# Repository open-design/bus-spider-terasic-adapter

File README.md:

UEXT adapter board for Terasic FPGA development boards with 40-pin expansion headers.

## Schematic

## BOM

| name | designation | designator | quantity | supply | datasheets |
| ---  | ---         | ---        | ---      | ---    | ---        |
| CONNFLY BH-10 | Conn_02x05_Odd_Even | J5,J2,J3,J4 | 4 |  [electronshik.ru](https://www.electronshik.ru/item/CONNFLY/BH-10)<br /> | [pdf](https://static.chipdip.ru/lib/463/DOC002463525.pdf) |
| CONNFLY BH-40 | Conn_02x20_Odd_Even | J1 | 1 |  [electronshik.ru](https://www.electronshik.ru/item/CONNFLY/BH-40)<br /> | [pdf](https://static.chipdip.ru/lib/463/DOC002463525.pdf) |
| Noname LED 1206 | LED | D1 | 1 |  [chipster.ru](https://chipster.ru/catalog/components/optic/leds/smd-led/3029.html)<br /> | no pdf |
| ONS MC14066BDR2G | 4066 | U2 | 1 |  [electronshik.ru](https://www.electronshik.ru/item/ONS/MC14066BDR2G)<br /> [digikey.com](https://www.digikey.com/products/en?keywords=MC14066BDR2G)<br /> [mouser.com](https://mouser.com/Search/Refine.aspx?Keyword=MC14066BDR2G)<br /> [farnell.com](https://uk.farnell.com/search?st=MC14066BDR2G)<br /> | [pdf](https://www.onsemi.com/pub/Collateral/MC14066B-D.PDF) |
| TI TPS79333-EP | TPS79333-EP | U1 | 1 |  [electronshik.ru](https://www.electronshik.ru/item/TI/TPS79333DBVR)<br /> [digikey.com](https://www.digikey.com/products/en?keywords=TPS79333DBVR)<br /> [mouser.com](https://mouser.com/Search/Refine.aspx?Keyword=TPS79333DBVR)<br /> [farnell.com](https://uk.farnell.com/search?st=TPS79333DBVR)<br /> | [pdf](http://www.ti.com/lit/ds/symlink/tps793.pdf) |
| YAGEO CC1206KKX7R8BB106 | 10uF | C3 | 1 |  [electronshik.ru](https://www.electronshik.ru/item/YAG/CC1206KKX7R8BB106)<br /> [digikey.com](https://www.digikey.com/products/en?keywords=CC1206KKX7R8BB106)<br /> [mouser.com](https://mouser.com/Search/Refine.aspx?Keyword=CC1206KKX7R8BB106)<br /> [farnell.com](https://uk.farnell.com/search?st=CC1206KKX7R8BB106)<br /> | [pdf](http://www.yageo.com/exep/pages/download/literatures/ProductSelectionGuide_2018_Final.pdf#page=112) |
| YAGEO CC1206KRX7R9BB103 | 10nF | C2 | 1 |  [electronshik.ru](https://www.electronshik.ru/item/YAG/CC1206KRX7R9BB103)<br /> [digikey.com](https://www.digikey.com/products/en?keywords=CC1206KRX7R9BB103)<br /> [mouser.com](https://mouser.com/Search/Refine.aspx?Keyword=CC1206KRX7R9BB103)<br /> [farnell.com](https://uk.farnell.com/search?st=CC1206KRX7R9BB103)<br /> | [pdf](http://www.yageo.com/exep/pages/download/literatures/ProductSelectionGuide_2018_Final.pdf#page=112) |
| YAGEO CC1206KRX7R9BB104 | 0.1uF | C1,C4 | 2 |  [electronshik.ru](https://www.electronshik.ru/item/YAG/CC1206KRX7R9BB104)<br /> [digikey.com](https://www.digikey.com/products/en?keywords=CC1206KRX7R9BB104)<br /> [mouser.com](https://mouser.com/Search/Refine.aspx?Keyword=CC1206KRX7R9BB104)<br /> [farnell.com](https://uk.farnell.com/search?st=CC1206KRX7R9BB104)<br /> | [pdf](http://www.yageo.com/exep/pages/download/literatures/ProductSelectionGuide_2018_Final.pdf#page=112) |
| YAGEO RC1206FR-0710KL | 10K | R3,R4 | 2 |  [electronshik.ru](https://www.electronshik.ru/item/YAG/RC1206FR-0710KL)<br /> [digikey.com](https://www.digikey.com/products/en?keywords=RC1206FR-0710KL)<br /> [mouser.com](https://mouser.com/Search/Refine.aspx?Keyword=RC1206FR-0710KL)<br /> [farnell.com](https://uk.farnell.com/search?st=RC1206FR-0710KL)<br /> | [pdf](http://www.yageo.com/exep/pages/download/literatures/ProductSelectionGuide_2018_Final.pdf#page=8) |
| YAGEO RC1206FR-071K1L | 1.1K | R2 | 1 |  [electronshik.ru](https://www.electronshik.ru/item/YAG/RC1206FR-071K1L)<br /> [digikey.com](https://www.digikey.com/products/en?keywords=RC1206FR-071K1L)<br /> [mouser.com](https://mouser.com/Search/Refine.aspx?Keyword=RC1206FR-071K1L)<br /> [farnell.com](https://uk.farnell.com/search?st=RC1206FR-071K1L)<br /> | [pdf](http://www.yageo.com/exep/pages/download/literatures/ProductSelectionGuide_2018_Final.pdf#page=8) |
| YAGEO RC1206FR-074K7L | 4.7K | R1 | 1 |  [electronshik.ru](https://www.electronshik.ru/item/YAG/RC1206FR-074K7L)<br /> [digikey.com](https://www.digikey.com/products/en?keywords=RC1206FR-074K7L)<br /> [mouser.com](https://mouser.com/Search/Refine.aspx?Keyword=RC1206FR-074K7L)<br /> [farnell.com](https://uk.farnell.com/search?st=RC1206FR-074K7L)<br /> | [pdf](http://www.yageo.com/exep/pages/download/literatures/ProductSelectionGuide_2018_Final.pdf#page=8) |

## Links

* [InnovateFPGA 2018 | EM099 | Bus Spider](http://www.innovatefpga.com/cgi-bin/innovate/teams2018.pl?Id=EM099)
* [Bus Spider: flexible open source hacker multi-tool](https://github.com/miet-riscv-workgroup/de10-nano-bus-spider)
* [Olimex UEXT board to board connector](https://www.olimex.com/Products/Modules/UEXT/)
* [Dangerous Prototypes: Bus Pirate v3.6](http://dangerousprototypes.com/docs/Bus_Pirate_v3.6)

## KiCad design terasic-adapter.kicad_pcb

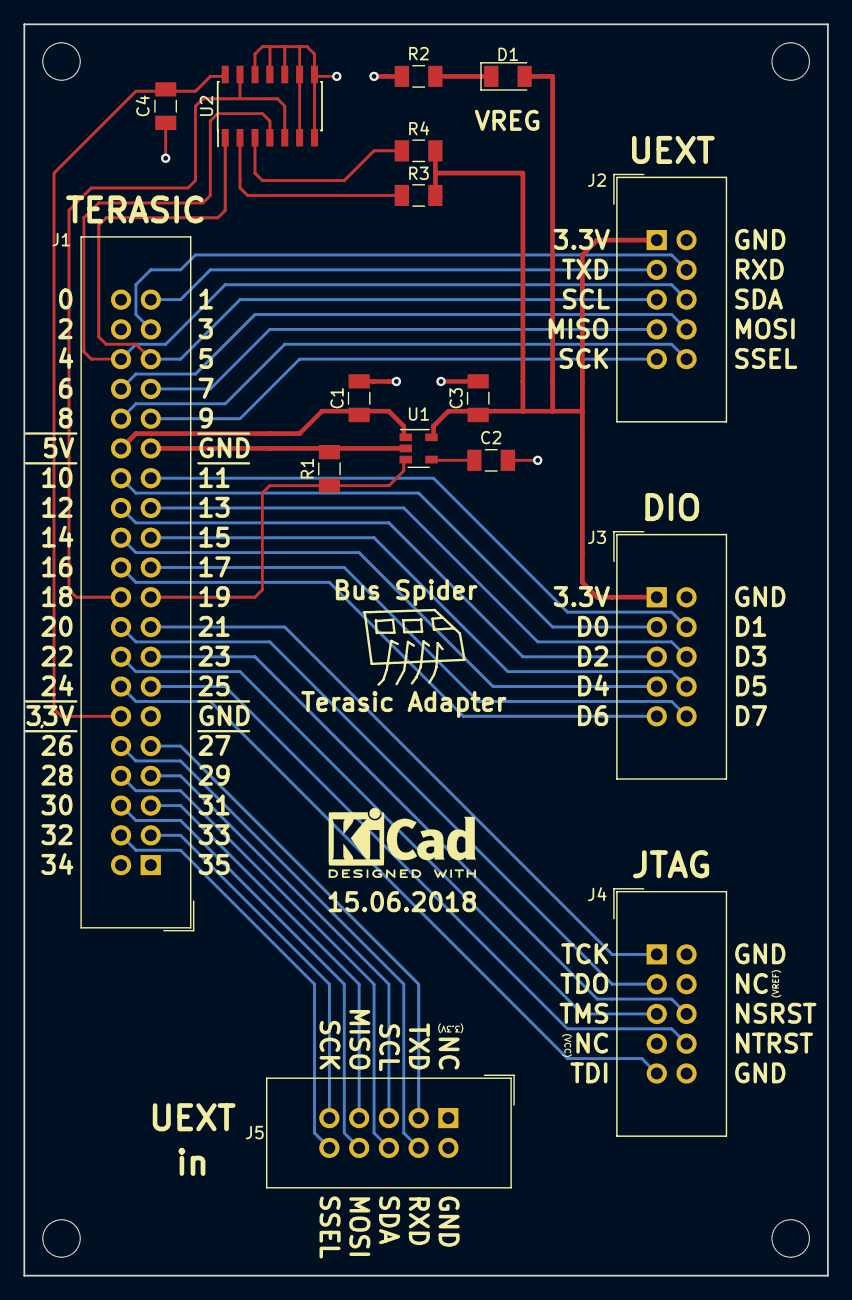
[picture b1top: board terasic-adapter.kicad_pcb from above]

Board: 2 copper layers, 68.6 x 106.8 mm, 20 parts (0 on the bottom side), 40 nets.

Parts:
C1, C4: 0.1uF; C_1206_3216Metric
C2: 10nF; C_1206_3216Metric
C3: 10uF; C_1206_3216Metric
D1: LED; LED_1206_3216Metric
J1: Conn_02x20_Odd_Even; IDC-Header_2x20_P2.54mm_Vertical
J2, J3, J4, J5: Conn_02x05_Odd_Even; IDC-Header_2x05_P2.54mm_Vertical
MK1, MK2, MK3, MK4: Mounting_Hole; MountingHole_3.2mm_M3
R1: 4.7K; R_1206_3216Metric
R2: 1.1K; R_1206_3216Metric
R3, R4: 10K; R_1206_3216Metric
U1: TPS79333-EP; SOT-23-5
U2: 4066; SOIC-14_3.9x8.7mm_P1.27mm

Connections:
+3V3: C4.2, J1.12, U2.14
+5V: C1.1, J1.30, U1.1
/GPIO1: J1.39, J2.3
/GPIO3: J1.37, J2.4
/GPIO4: J1.36, J2.6, U2.4
/GPIO5: J1.35, J2.5, U2.1
/GPIO6: J1.34, J2.8
/GPIO7: J1.33, J2.7
/GPIO8: J1.32, J2.10
/GPIO9: J1.31, J2.9
/GPIO10: J1.28, J3.3
/GPIO11: J1.27, J3.4
/GPIO12: J1.26, J3.5
/GPIO13: J1.25, J3.6
/GPIO14: J1.24, J3.7
/GPIO15: J1.23, J3.8
/GPIO16: J1.22, J3.9
/GPIO17: J1.21, J3.10
/GPIO18: J1.20, U2.5, U2.13
/GPIO19: J1.19, R1.1, U1.3
/GPIO20: J1.18, J4.3
/GPIO21: J1.17, J4.1
/GPIO22: J1.16, J4.5
/GPIO23: J1.15, J4.6
/GPIO24: J1.14, J4.9
/GPIO25: J1.13, J4.8
/GPIO26: J1.10, J5.4
/GPIO27: J1.9, J5.3
/GPIO28: J1.8, J5.6
/GPIO29: J1.7, J5.5
/GPIO30: J1.6, J5.8
/GPIO31: J1.5, J5.7
/GPIO32: J1.4, J5.10
/GPIO33: J1.3, J5.9
/PWR3V3: C3.1, D1.2, J2.1, J3.1, R3.2, R4.2, U1.5
GND: C1.2, C2.2, C3.2, C4.1, J1.11, J1.29, J2.2, J3.2, J4.2, J4.10, J5.2, R1.2, R2.2, U1.2, U2.6, U2.7, U2.8, U2.9, U2.10, U2.11, U2.12
unnamed: C2.1, U1.4
unnamed: D1.1, R2.1
unnamed: R3.1, U2.2
unnamed: R4.1, U2.3

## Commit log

2019-01-05 Import kicad scripts by Scott Bezek
    Original Scott Bezek's scripts can be found here:
    https://github.com/scottbez1/splitflap/tree/master/electronics/
    Usage:
    ./scripts/generate_gerber.py terasic-adapter.kicad_pcb
    ./scripts/generate_pdf.py terasic-adapter.kicad_pcb
    ./scripts/generate_svg.py terasic-adapter.kicad_pcb
2019-01-05 terasic-adapter.sch: adapt mounting holes for Debian kicad-symbols 5.0.2-1
    See this kicad-symbols commit for details:
    | commit d4764750700ab725bbe5e3e0cd33c768fa56a677
    | Author: Antonio Vázquez <antoniovazquezblanco@gmail.com>
    | Date: Wed May 23 12:43:00 2018 +0200
    |
    | Mechanical: Rename mounting holes to be consistent and update FPFilters
2019-01-07 add parse_csv_bom.py script
    Usage:
    # In PCB Layout Editor
    # File -> Fabrication Outputs -> BOM File -> Save terasic-adapter.csv
    BOARD_NAME=terasic-adapter
    BOM=build/${BOARD_NAME}-bom
    mkdir -p build
2019-01-07 README.md: add BOM generated by parse_csv_bom.py
2019-01-07 add pcb 3D view and schematic pictures
2019-05-05 fix part spelling for TPS79333-EP
    Fixed in upstream https://github.com/kicad/kicad-symbols
    by commit 5da4de5bcafbec757f83fc1941268a7594b1ae7c
    (fix part spelling for TPS79333-EP)
2019-06-25 README.md: fixup InnovateFPGA 2018 | EM099 | Bus Spider link
2020-02-06 scripts: use python3
